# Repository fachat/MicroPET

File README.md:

# uPET R2

# NOTE: the newer version is in the [cbm_micropet](https://github.com/fachat/cbm_micropet) repository!

This is a re-incarnation of the Commodore PET computer(s) from the later 1970s.

It is build on a Eurocard board and has only parts that can still be obtained new in 2021.
The current version is 2.0B.

Here is the [Overview video](https://youtu.be/COlfqcaY7rI)

Some more videos on the build process can be found here [YT 8-bit times](https://youtube.com/playlist?list=PLi1dzy7kw1iybjcUccgjCV4fhNH4IPWSx)

## Features

The board is built with a number of features:

- Commodore 3032 / 4032 / 8032 / 8296 with options menu to select at boot
  - Boot-menu to select different PET versions to run (BASIC 1, 2, 4)
  - 40 col character display
  - 80 col character display
  - 8296 memory map emulation
  - IEEE488 interface (card edge and 24pin flat ribbon cable)
  - Tape connector (card edge)
  - PET graphics keyboard, or alternatively a C64 keyboard
- Improved system design:
  - 512k video RAM, plus 512k fast RAM, accessible using banks on the W65816 CPU
  - boot from an SPI Flash ROM
  - up to 12.5 MHz mode (via configuration register)
  - VGA b/w video output
  - Write protection for the PET ROMs once copied to RAM
  - lower 32k RAM mappable from all of the 512k fast RAM
- Improved Video output:
  - Hires graphics mode (using a configuration register)
  - modifyable character set
  - 40/80 column display switchable
  - 25/50 rows display switch
  - multiple video pages mappable to $8000 video mem address

## Overview

The system architecture is actually rather simple, as you can see in the following graphics.

The main functionality is "hidden" inside the CPLD. It does:

1. clock generation and management
2. memory mapping
3. video generation.
4. SPI interface and boot

On the CPU side of the CPLD it is actually a rather almost normal 65816 computer, 
with the exception that the bank register (that catches and stores the address lines 
A16-23 from the CPU's data bus) is in the CPLD, and that there is no ROM. The ROM has been
replaced with some code in the CPLD that copies the initial program to the CPU accessible
RAM, taking it from the Flash Boot ROM via SPI. This actually simplifies the design,
as 

1. parallel ROMs are getting harder to come by and
2. they are typically not as fast as is needed, and
3. with the SPI boot they don't occupy valuable CPU address space.

The video generation is done using time-sharing access to the video RAM.
The VGA output is 640x480 at 60Hz. So there is a 40ns slot per pixel on the screen, 
with a pixel clock of 25MHz.

The system runs at 12.5MHz, so a byte of pixel output (i.e. eight pixels) has four
memory accesses to VRAM. Two of them are reserved for video access, one for fetching the
character data (e.g. at $08xxx in the PET), and the second one to fetch the "character ROM"
data, i.e. the pixel data for a character. This is also stored in VRAM, and is being loaded
there from the Flash Boot ROM by the initial boot loader.

The CPLD reads the character data, stores it to fetch the character pixel data, and streams
that out using its internal video shift register.

For more detailled descriptions of the features and how to use them, pls see the subdirectory,
as described in the next section.

## Building

Here are four subdirectories:

- [Board](Board/) that contains the board schematics and layout
- [CPLD](CPLD/) contains the VHDL code to program the CPLD logic chip used, and describes the configuration options - including the [SPI](CPLD/SPI.md) usage
- [ROM](ROM/) ROM contents to boot
- [Case](Case/) 3-D printed supports and keyboards to mount board in a C64c case

### Board

To build the board, you have to find a provider that builds PCBs from Eagle .brd files.
Currently no gerbers are provided.

### CPLD

The CPLD is a Xilinx xc95288xl programmable logic chip. It runs on 3.3V, but is 5V tolerant,
so can be directly connected to 5V TTL chips. I programmed it in VHDL.

Unfortunately the W65xx parts are "only" CMOS, and not TTL input chips - but 3.3V is still above
the VCC/2 for the 5V chips. Only Phi2 needs improvements on the signal quality using a pull-up resistor
and specific VHDL programming.

### ROM

The ROM image can be built using gcc, xa65, and make. Use your favourite EPROM programmer to burn it into the SPI Flash chip.

The ROM contains images of all required ROM images for BASIC 1, 2, and 4, and corresponding editor ROMs, including
some that have been extended with wedges.

The updated editor ROMs are from [Steve's Editor ROM project](http://www.6502.org/users/sjgray/projects/editrom/index.html) and can handle C64 keyboards, has a DOS wedge included, and resets into the Micro-PET boot menu.
For more details see the [ROM description](ROM/README.md)

## Future Plans

These are future expansions I want to look into. Not all may be possible to implement.

- n/a

## Gallery

Note: the published schematics and board has the extra wires fixed/included.

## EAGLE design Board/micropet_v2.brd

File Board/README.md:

# Board V2.1A

The board is a two-layer Eurocard, i.e. 160mm x 100mm.

## Schematics & Layout

The schematics and layout have been created with Cadsoft Eagle.
So, here you can find the 

- [micropet_v2.sch](micropet_v2.sch) and
- [micropet_v2.brd](micropet_v2.brd) files

But, you can still have a look at the schematics and layout using the
PNG images created

- [micropet_v2-sch-1.png](micropet_v2-sch-1.png) Part 1 - PETIO
- [micropet_v2-sch-2.png](micropet_v2-sch-2.png) Part 2 - CPLD, CPU, RAM
- [micropet_v2-sch-3.png](micropet_v2-sch-3.png) Part 3 - Power
- [micropet_v2-sch-4.png](micropet_v2-sch-4.png) Part 4 - Video and Audio output
- [micropet_v2-sch-5.png](micropet_v2-sch-5.png) Part 5 - SPI devices (Eth, USB, RTCC, ...)

## Bill of Material

The main chips are:

- 1x W65816S CPU
- 2x W65C21N PIA
- 1x W65C22N VIA

- 1x xc95288xl CPLD
- 2x 8x512k parallel SRAM with 25ns access time
- 2x 74LS641-1
- 1x 74LS145 4-to-10 BCD O.C. driver (keyboard)
- 1x 74LS07
- 1x DS1813 RESET controller

- 50 MHZ crystal oscillator

- Voltage regulator

- x 0.1uF bypass caps

- 5.1kOhm / 2.4kOhm pairs of resistor arrays for IEEE488
- 10kOhm pullup
- 1x 1kOhm pullup
- 1x 8x10kOhm resistor array (keyboard pull up)

- div. resistors/caps to generate 3.3V output

More details can be found in the [Eagle parts list](micropet_v2.parts).

## Changelog

### V2.1A

In this version I incorporated the fixes I had to apply to the first prototype board. Also, I changed the IEEE488 circuit such that it can now really work as a disk drive for another PET. This brings it in line with the CSA PETIO 1.2A/1.3A boards that have this functionaly fixed.

## Erratum

This section describes fixes from my 2.0A prototype board, and these are the cuts/additional wires you see on the pictures, where I fixed my 2.0A boards.

### 2.0C

- I pulled up /IRQ to 5V, but that was potentially backfeeding to the 3.3V SPI devices. A pull-up to 3.3V still worked just fine without problems

### 2.0B

- In 2.0A I planned to use the 74245 to drive the system's Phi2 clocks (CPU & I/O), and to level-shift it. But it turned out that this was not stable, so I reverted to the pull-up resistor method again
- I was missing a cross-sheet connection for the I/O Phi2 clock
- Also I was missing the SPI select line for the RTCC

- 
-

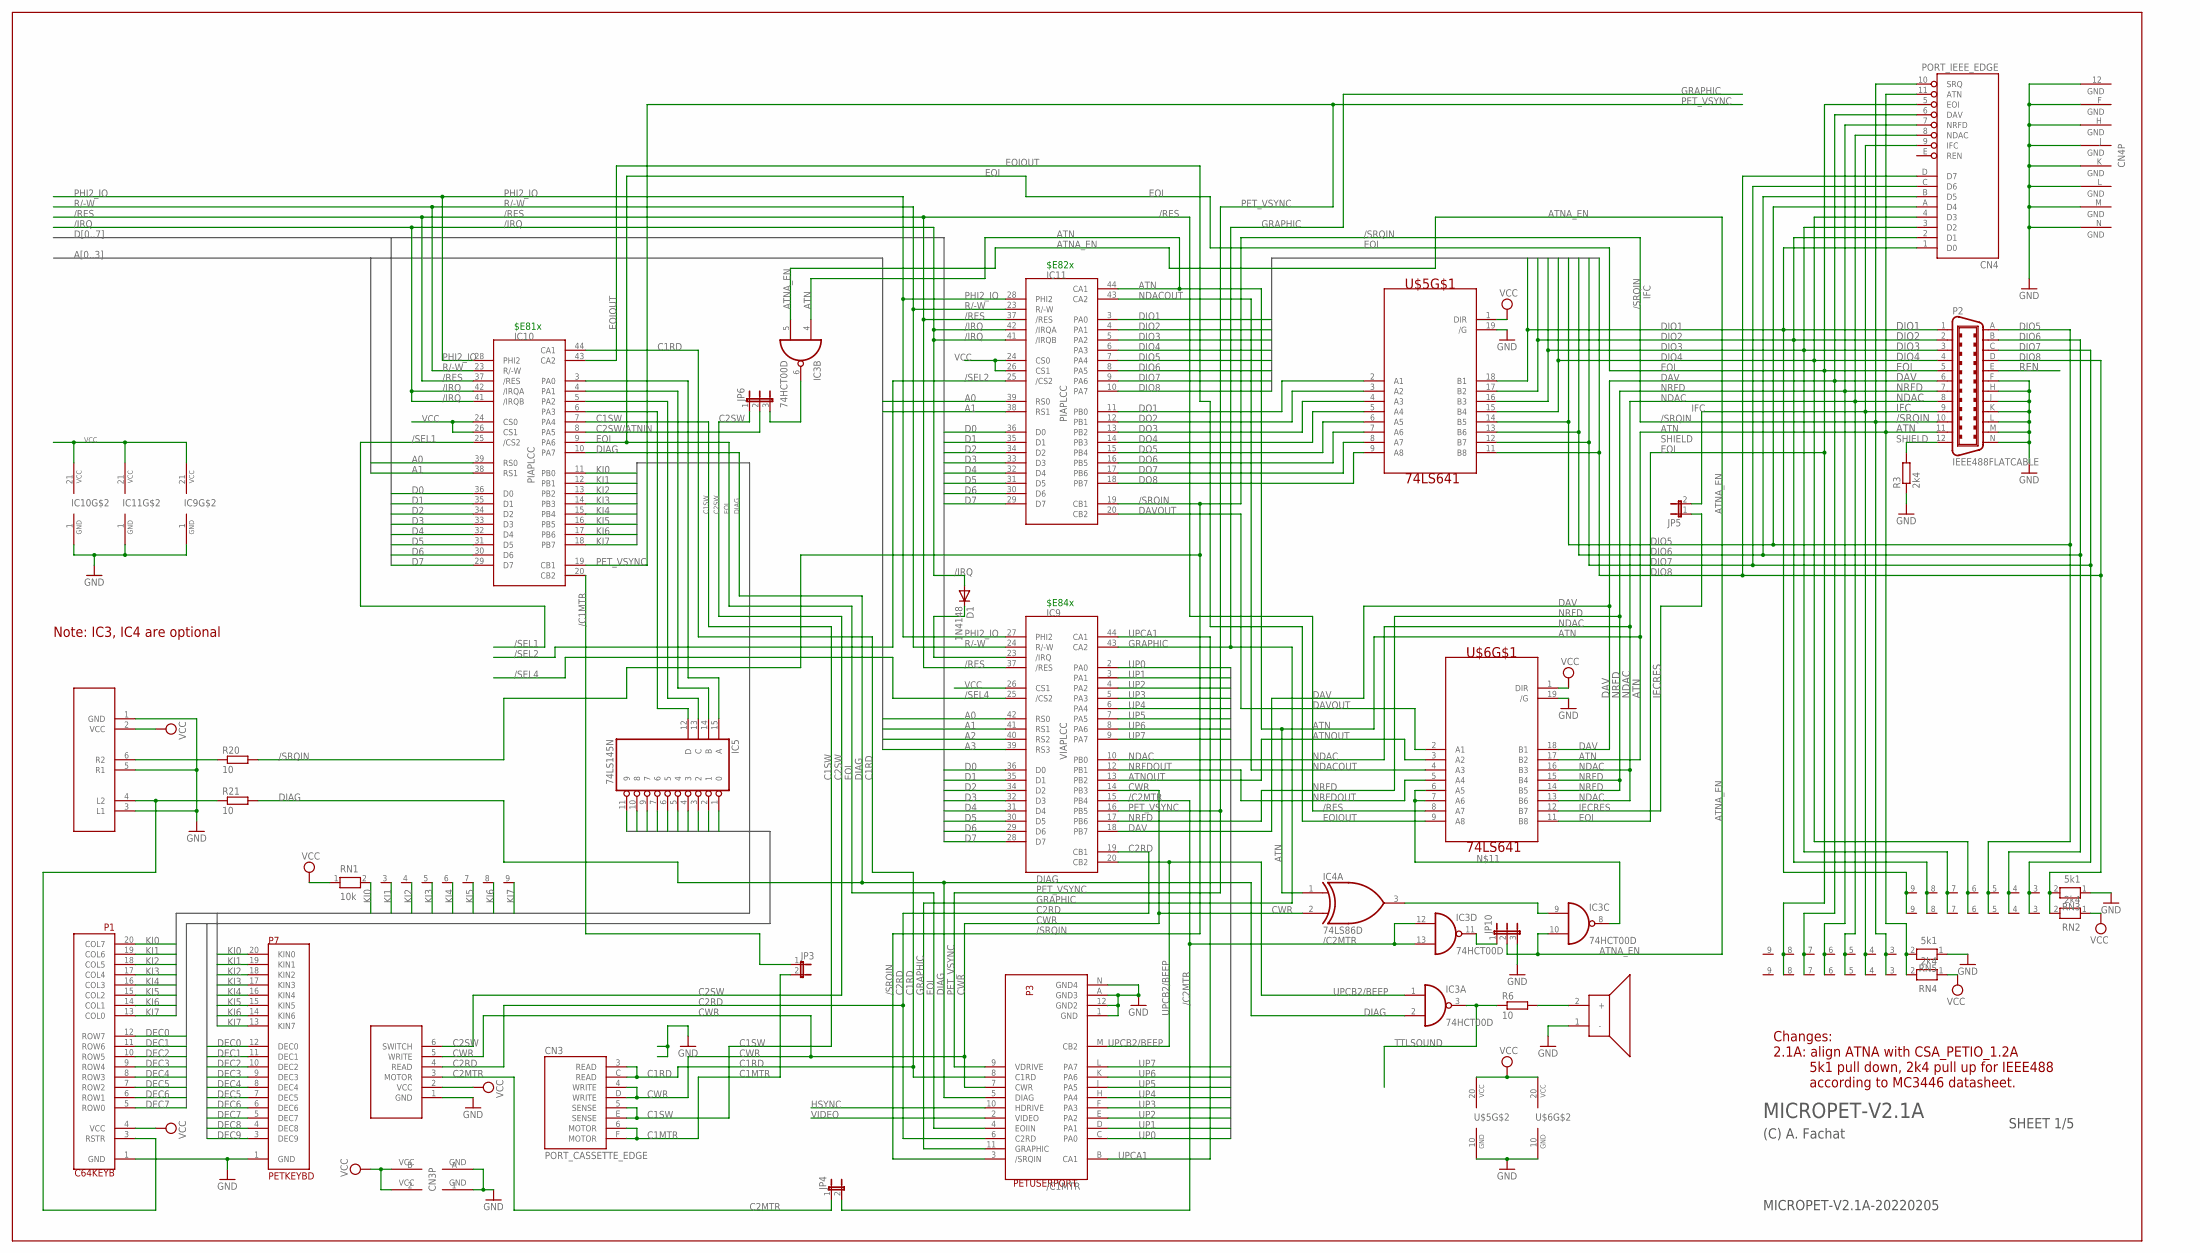
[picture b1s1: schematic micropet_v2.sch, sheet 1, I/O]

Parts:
BEEP1: PIEZOBEEPER; JP2
CN3: PORT_CASSETTE_EDGE; MA156_6-2_KEYED
CN4: PORT_IEEE_EDGE; MA156_12-2_IEEE
D1: 1N4148; D-5
IC3: 74HCT00D; SO14
IC4: 74LS86D; SO14
IC5: 74LS145N; DIL16
IC9: VIAPLCC; PLCC44
IC10, IC11: PIAPLCC; PLCC44
JP3, JP4, JP5: JP1E; JP1
JP6, JP10: JP2E; JP2
P1: C64KEYB
P2: IEEE488FLATCABLE; FLAT24
P3: PETUSERPORT; FLAT24
P6: CBMTAPE; JP6
P7: PETKEYBD; C64KEYB
R3: 2k4; 0207/2V
R6, R20, R21: 10; 0207/2V
RN1: 10k; RN-9
RN2, RN4: 2k4; RN-9
RN3, RN5: 5k1; RN-9
U$5, U$6: 74LS641; DIL20
U$11: PETSKEY_EXTRA; JP6

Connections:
/C1MTR: IC10.20 (CB2), JP3.1
/C2MTR: IC3.12 (I0), IC3.13 (I1), IC9.15 (PB4), JP4.2
/IRQ: D1.A, IC10.41 (/IRQB), IC10.42 (/IRQA), IC11.41 (/IRQB), IC11.42 (/IRQA); also elsewhere on the board
/RES: IC9.37 (/RES), IC10.37 (/RES), IC11.37 (/RES), U$6.8 (A7); also elsewhere on the board
/SEL1: IC10.25 (/CS2); also elsewhere on the board
/SEL2: IC11.25 (/CS2); also elsewhere on the board
/SEL4: IC9.25 (/CS2); also elsewhere on the board
/SRQIN: CN4.10 (SRQ), IC11.19 (CB1), P2.10, P3.3 (/SRQIN), R20.2, RN4.3, RN5.3
A0: IC9.42 (RS0), IC10.39 (RS0), IC11.39 (RS0); also elsewhere on the board
A1: IC9.41 (RS1), IC10.38 (RS1), IC11.38 (RS1); also elsewhere on the board
A2: IC9.40 (RS2); also elsewhere on the board
A3: IC9.39 (RS3); also elsewhere on the board
ATN: CN4.11 (ATN), IC3.4 (I0), IC4.1 (I0), IC11.44 (CA1), P2.11, RN4.2, RN5.2, U$6.17 (B2)
ATNA_EN: IC3.5 (I1), IC3.10 (I1), JP10.2
ATNOUT: IC9.13 (PB2), U$6.3 (A2)
C1MTR: CN3.6 (MOTOR), CN3.F (MOTOR), JP3.2
C1RD: CN3.3 (READ), CN3.C (READ), IC10.44 (CA1), P3.8 (C1RD)
C1SW: CN3.5 (SENSE), CN3.E (SENSE), IC10.7 (PA4)
C2MTR: JP4.1, P6.3 (MOTOR)
C2RD: IC9.19 (CB1), P3.6 (C2RD), P6.4 (READ)
C2SW: JP6.1, P6.6 (SWITCH)
C2SW/ATNIN: IC10.8 (PA5), JP6.2
CWR: CN3.4 (WRITE), CN3.D (WRITE), IC4.2 (I1), IC9.14 (PB3), P3.7 (CWR), P6.5 (WRITE)
D0: IC9.36 (D0), IC10.36 (D0), IC11.36 (D0); also elsewhere on the board
D1: IC9.35 (D1), IC10.35 (D1), IC11.35 (D1); also elsewhere on the board
D2: IC9.34 (D2), IC10.34 (D2), IC11.34 (D2); also elsewhere on the board
D3: IC9.32 (D3), IC10.33 (D3), IC11.33 (D3); also elsewhere on the board
D4: IC9.31 (D4), IC10.32 (D4), IC11.32 (D4); also elsewhere on the board
D5: IC9.30 (D5), IC10.31 (D5), IC11.31 (D5); also elsewhere on the board
D6: IC9.29 (D6), IC10.30 (D6), IC11.30 (D6); also elsewhere on the board
D7: IC9.28 (D7), IC10.29 (D7), IC11.29 (D7); also elsewhere on the board
DAV: CN4.6 (DAV), IC9.18 (PB7), P2.6, RN4.7, RN5.7, U$6.18 (B1)
DAVOUT: IC11.20 (CB2), U$6.2 (A1)
DEC0: IC5.1 (0), P1.12 (ROW7), P7.12 (DEC0)
DEC1: IC5.2 (1), P1.11 (ROW6), P7.11 (DEC1)
DEC2: IC5.3 (2), P1.10 (ROW5), P7.10 (DEC2)
DEC3: IC5.4 (3), P1.9 (ROW4), P7.9 (DEC3)
DEC4: IC5.5 (4), P1.8 (ROW3), P7.8 (DEC4)
DEC5: IC5.6 (5), P1.7 (ROW2), P7.7 (DEC5)
DEC6: IC5.7 (6), P1.6 (ROW1), P7.6 (DEC6)
DEC7: IC5.9 (7), P1.5 (ROW0), P7.5 (DEC7)
DEC8: IC5.10 (8), P7.4 (DEC8)
DEC9: IC5.11 (9), P7.3 (DEC9)
DIAG: IC3.2 (I1), IC10.10 (PA7), P3.5 (DIAG), R21.2
DIO1: CN4.1 (D0), IC11.3 (PA0), P2.1, RN2.9, RN3.9, U$5.18 (B1)
DIO2: CN4.2 (D1), IC11.4 (PA1), P2.2, RN2.8, RN3.8, U$5.17 (B2)
DIO3: CN4.3 (D2), IC11.5 (PA2), P2.3, RN2.7, RN3.7, U$5.16 (B3)
DIO4: CN4.4 (D3), IC11.6 (PA3), P2.4, RN2.6, RN3.6, U$5.15 (B4)
DIO5: CN4.A (D4), IC11.7 (PA4), P2.A (13), RN2.5, RN3.5, U$5.14 (B5)
DIO6: CN4.B (D5), IC11.8 (PA5), P2.B (14), RN2.4, RN3.4, U$5.13 (B6)
DIO7: CN4.C (D6), IC11.9 (PA6), P2.C (15), RN2.3, RN3.3, U$5.12 (B7)
DIO8: CN4.D (D7), IC11.10 (PA7), P2.D (16), RN2.2, RN3.2, U$5.11 (B8)
DO1: IC11.11 (PB0), U$5.2 (A1)
DO2: IC11.12 (PB1), U$5.3 (A2)
DO3: IC11.13 (PB2), U$5.4 (A3)
DO4: IC11.14 (PB3), U$5.5 (A4)
DO5: IC11.15 (PB4), U$5.6 (A5)
DO6: IC11.16 (PB5), U$5.7 (A6)
DO7: IC11.17 (PB6), U$5.8 (A7)
DO8: IC11.18 (PB7), U$5.9 (A8)
EOI: CN4.5 (EOI), IC10.9 (PA6), P2.5, P3.4 (EOIIN), RN4.8, RN5.8, U$6.11 (B8)
EOIOUT: IC10.43 (CA2), U$6.9 (A8)
GND: BEEP1.1 (-), CN3.1 (GND), CN3.A (GND), CN4.12 (GND), CN4.F (GND), CN4.H (GND), CN4.J (GND), CN4.K (GND), CN4.L (GND), CN4.M (GND), CN4.N (GND), IC3.7 (GND), IC4.7 (GND), IC5.8 (GND), IC9.1 (GND), IC10.1 (GND), IC11.1 (GND), JP10.3, P1.1 (GND), P2.F (18), P2.H (19), P2.J (20), P2.K (21), P2.L (22), P2.M (23), P2.N (24), P3.1 (GND), P3.12 (GND2), P3.A (GND3), P3.N (GND4), P6.1 (GND), P7.1 (GND), R3.1, RN3.1, RN5.1, U$5.10 (GND), U$5.19 (/G), U$6.10 (GND), U$6.19 (/G), U$11.1 (GND), U$11.3 (L1), U$11.5 (R1); also elsewhere on the board
GRAPHIC: IC9.43 (CA2), P3.11 (GRAPHIC); also elsewhere on the board
HSYNC: P3.10 (HDRIVE); also elsewhere on the board
IECRES: JP5.1, U$6.12 (B7)
IFC: CN4.9 (IFC), JP5.2, P2.9, RN4.4, RN5.4
KI0: IC10.11 (PB0), P1.20 (COL7), P7.20 (KIN0), RN1.2
KI1: IC10.12 (PB1), P1.19 (COL6), P7.19 (KIN1), RN1.3
KI2: IC10.13 (PB2), P1.18 (COL5), P7.18 (KIN2), RN1.4
KI3: IC10.14 (PB3), P1.17 (COL4), P7.17 (KIN3), RN1.5
KI4: IC10.15 (PB4), P1.16 (COL3), P7.16 (KIN4), RN1.6
KI5: IC10.16 (PB5), P1.15 (COL2), P7.15 (KIN5), RN1.7
KI6: IC10.17 (PB6), P1.14 (COL1), P7.14 (KIN6), RN1.8
KI7: IC10.18 (PB7), P1.13 (COL0), P7.13 (KIN7), RN1.9
unnamed: IC3.9 (I0), IC4.3 (O)
unnamed: IC3.11 (O), JP10.1
unnamed: BEEP1.2 (+), R6.2
unnamed: D1.C, IC9.23 (/IRQ)
unnamed: IC3.8 (O), U$6.6 (A5), U$6.7 (A6)
unnamed: IC3.6 (O), JP6.3
unnamed: IC5.15 (A), IC10.3 (PA0)
unnamed: IC5.14 (B), IC10.4 (PA1)
unnamed: IC5.13 (C), IC10.5 (PA2)
unnamed: IC5.12 (D), IC10.6 (PA3)
unnamed: P1.3 (RSTR), R21.1, U$11.4 (L2)
unnamed: R20.1, U$11.6 (R2)
NDAC: CN4.8 (NDAC), IC9.10 (PB0), P2.8, RN4.5, RN5.5, U$6.13 (B6), U$6.16 (B3)
NDACOUT: IC11.43 (CA2), U$6.4 (A3)
NRFD: CN4.7 (NRFD), IC9.17 (PB6), P2.7, RN4.6, RN5.6, U$6.14 (B5), U$6.15 (B4)
NRFDOUT: IC9.12 (PB1), U$6.5 (A4)
PET_VSYNC: IC9.16 (PB5), IC10.19 (CB1), P3.9 (VDRIVE); also elsewhere on the board
PHI2_IO: IC9.27 (PHI2), IC10.28 (PHI2), IC11.28 (PHI2); also elsewhere on the board
R/-W: IC9.24 (R/-W), IC10.23 (R/-W), IC11.23 (R/-W); also elsewhere on the board
REN: P2.E (17)
SHIELD: P2.12, R3.2
TTLSOUND: IC3.3 (O), R6.1; also elsewhere on the board
UP0: IC9.2 (PA0), P3.C (PA0)
UP1: IC9.3 (PA1), P3.D (PA1)
UP2: IC9.4 (PA2), P3.E (PA2)
UP3: IC9.5 (PA3), P3.F (PA3)
UP4: IC9.6 (PA4), P3.H (PA4)
UP5: IC9.7 (PA5), P3.J (PA5)
UP6: IC9.8 (PA6), P3.K (PA6)
UP7: IC9.9 (PA7), P3.L (PA7)
UPCA1: IC9.44 (CA1), P3.B (CA1)
UPCB2/BEEP: IC3.1 (I0), IC9.20 (CB2), P3.M (CB2)
VCC: CN3.2 (VCC), CN3.B (VCC), IC3.14 (VCC), IC4.14 (VCC), IC5.16 (VCC), IC9.21 (VCC), IC9.26 (CS1), IC10.21 (VCC), IC10.24 (CS0), IC10.26 (CS1), IC11.21 (VCC), IC11.24 (CS0), IC11.26 (CS1), P1.4 (VCC), P6.2 (VCC), RN1.1, RN2.1, RN4.1, U$5.1 (DIR), U$5.20 (VCC), U$6.1 (DIR), U$6.20 (VCC), U$11.2 (VCC); also elsewhere on the board
VIDEO: P3.2 (VIDEO); also elsewhere on the board

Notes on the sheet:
MICROPET-V2.1A-20220205
MICROPET-V2.1A
(C) A. Fachat
$E82x
$E84x
$E81x
SHEET 1/5
Note: IC3, IC4 are optional
Changes: 2.1A: align ATNA with CSA_PETIO_1.2A 5k1 pull down, 2k4 pull up for IEEE488 according to MC3446 datasheet.

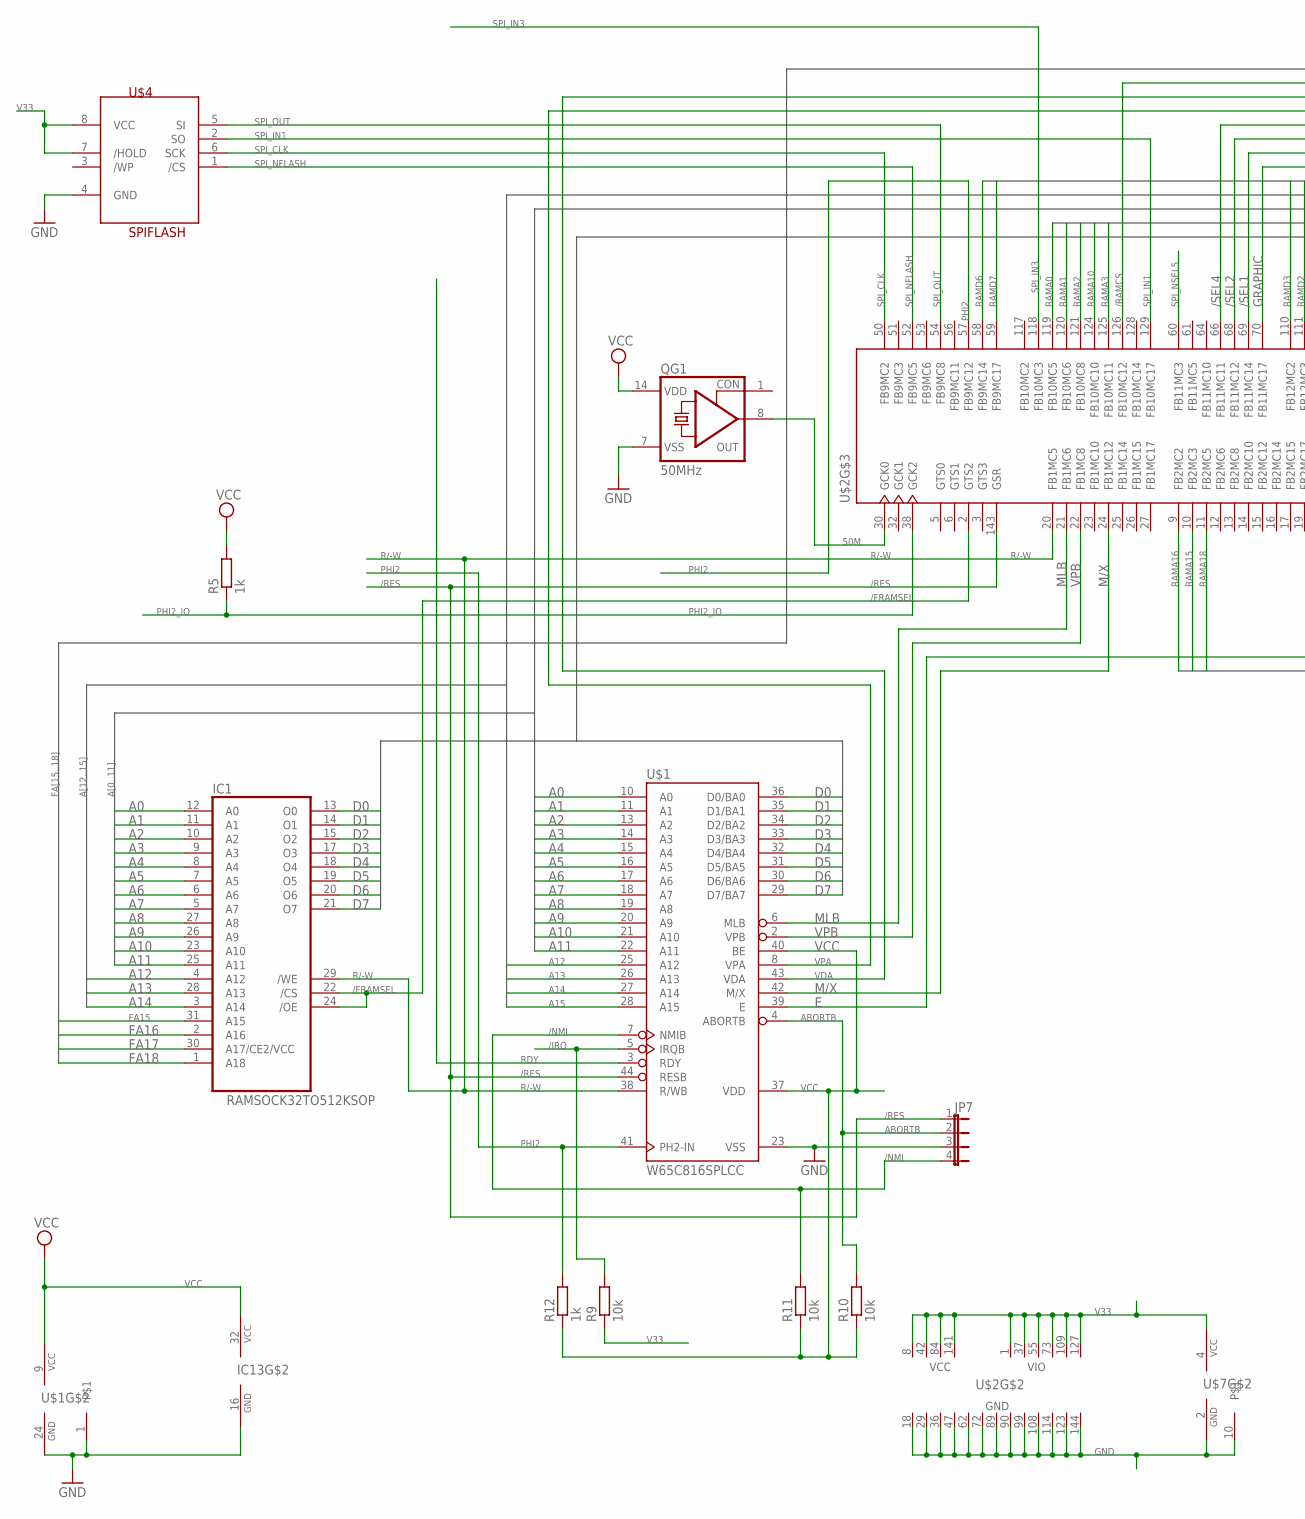
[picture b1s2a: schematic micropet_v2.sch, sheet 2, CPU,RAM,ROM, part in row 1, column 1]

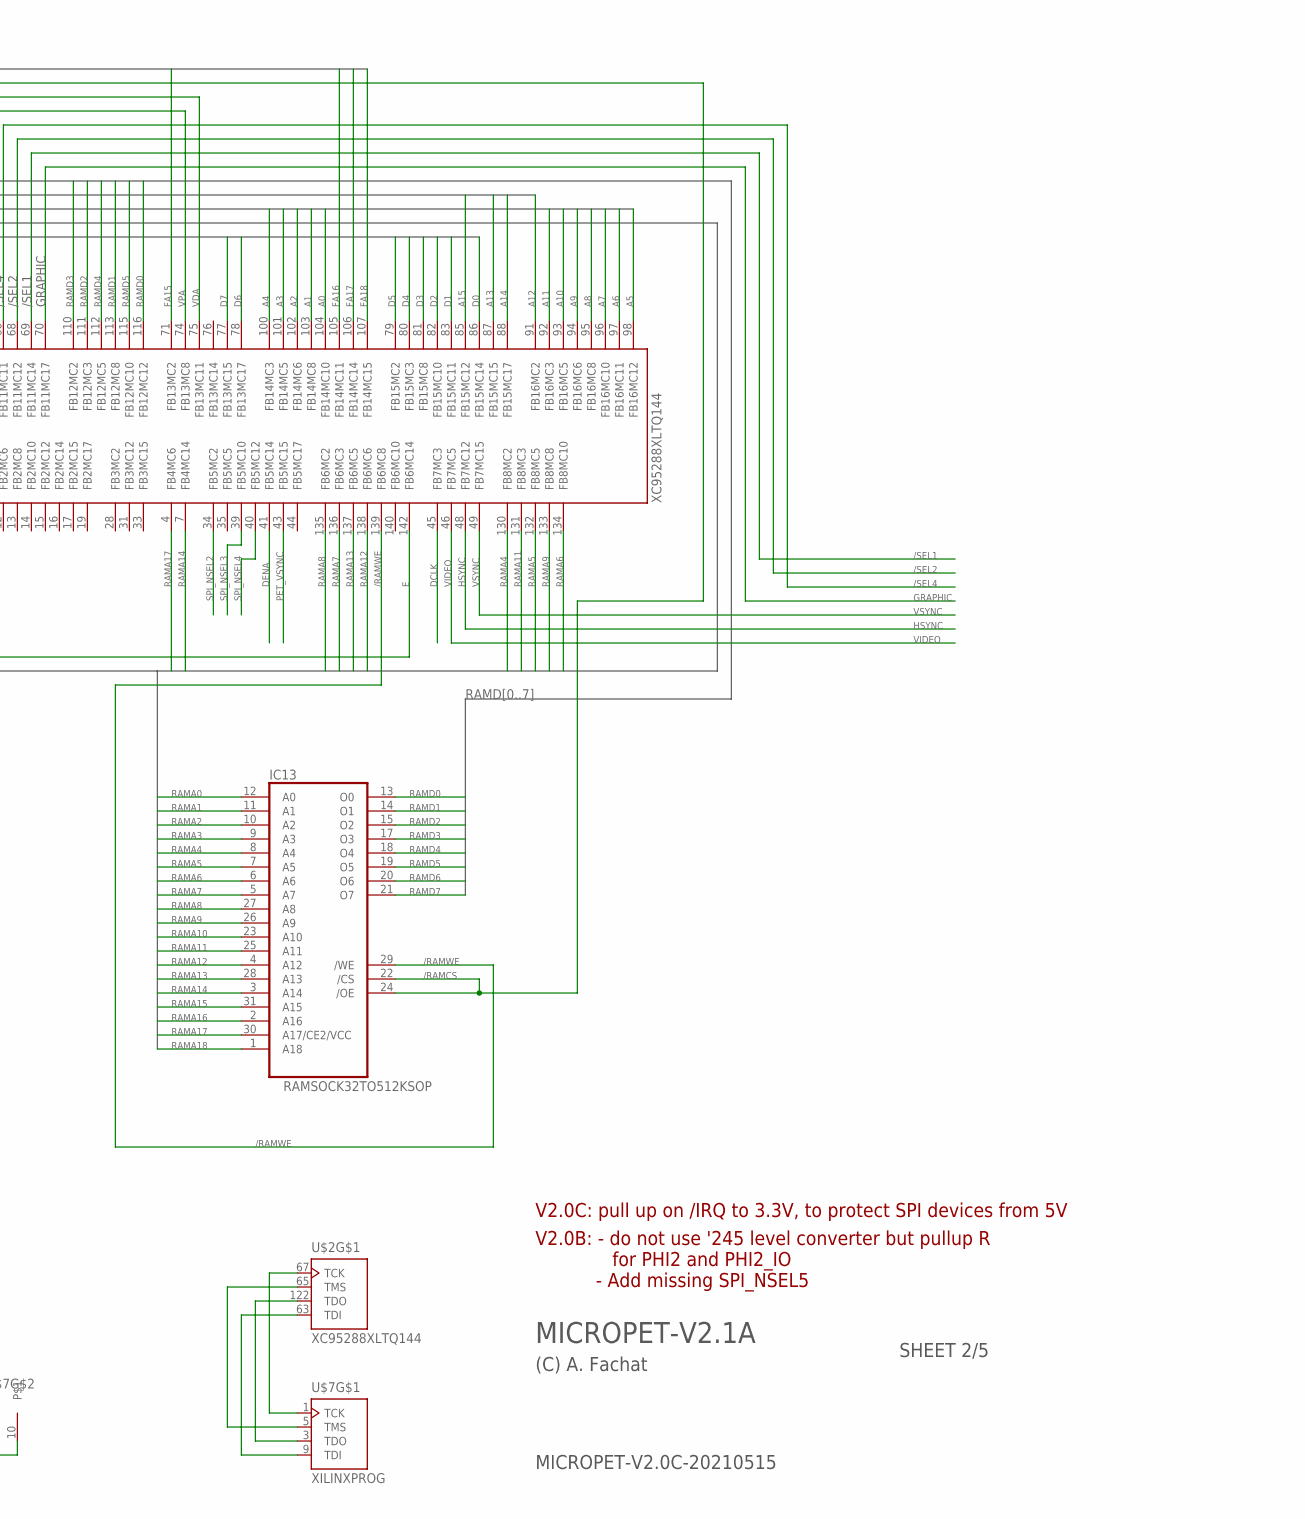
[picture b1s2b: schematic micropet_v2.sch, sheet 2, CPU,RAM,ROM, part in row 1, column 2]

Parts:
IC1, IC13: RAMSOCK32TO512KSOP; SOP32
JP7: JP4E; JP4
QG1: 50MHz; SG51
R5, R12: 1k; 0207/2V
R9, R10, R11: 10k; 0207/2V
U$1: W65C816SPLCC; PLCC44
U$2: XC95288XLTQ144; TQFP144
U$4: SPIFLASH; DIL08
U$7: XILINXPROG; FLAT10BOX

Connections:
50M: QG1.8 (OUT), U$2.30 (GCK0)
/FRAMSEL: IC1.22 (/CS), IC1.24 (/OE), U$2.2 (GTS2)
/IRQ: R9.2, U$1.5 (IRQB); also elsewhere on the board
/NMI: JP7.4, R11.2, U$1.7 (NMIB)
/RAMCS: IC13.22 (/CS), IC13.24 (/OE), U$2.126 (FB10MC12)
/RAMWE: IC13.29 (/WE), U$2.139 (FB6MC8)
/RES: JP7.1, U$1.44 (RESB), U$2.143 (GSR); also elsewhere on the board
/SEL1: U$2.69 (FB11MC14); also elsewhere on the board
/SEL2: U$2.68 (FB11MC12); also elsewhere on the board
/SEL4: U$2.66 (FB11MC11); also elsewhere on the board
A0: IC1.12 (A0), U$1.10 (A0), U$2.104 (FB14MC10); also elsewhere on the board
A1: IC1.11 (A1), U$1.11 (A1), U$2.103 (FB14MC8); also elsewhere on the board
A2: IC1.10 (A2), U$1.13 (A2), U$2.102 (FB14MC6); also elsewhere on the board
A3: IC1.9 (A3), U$1.14 (A3), U$2.101 (FB14MC5); also elsewhere on the board
A4: IC1.8 (A4), U$1.15 (A4), U$2.100 (FB14MC3)
A5: IC1.7 (A5), U$1.16 (A5), U$2.98 (FB16MC12)
A6: IC1.6 (A6), U$1.17 (A6), U$2.97 (FB16MC11)
A7: IC1.5 (A7), U$1.18 (A7), U$2.96 (FB16MC10)
A8: IC1.27 (A8), U$1.19 (A8), U$2.95 (FB16MC8)
A9: IC1.26 (A9), U$1.20 (A9), U$2.94 (FB16MC6)
A10: IC1.23 (A10), U$1.21 (A10), U$2.93 (FB16MC5)
A11: IC1.25 (A11), U$1.22 (A11), U$2.92 (FB16MC3)
A12: IC1.4 (A12), U$1.25 (A12), U$2.91 (FB16MC2)
A13: IC1.28 (A13), U$1.26 (A13), U$2.87 (FB15MC15)
A14: IC1.3 (A14), U$1.27 (A14), U$2.88 (FB15MC17)
A15: U$1.28 (A15), U$2.85 (FB15MC12)
ABORTB: JP7.2, R10.2, U$1.4 (ABORTB)
D0: IC1.13 (O0), U$1.36 (D0/BA0), U$2.86 (FB15MC14); also elsewhere on the board
D1: IC1.14 (O1), U$1.35 (D1/BA1), U$2.83 (FB15MC11); also elsewhere on the board
D2: IC1.15 (O2), U$1.34 (D2/BA2), U$2.82 (FB15MC10); also elsewhere on the board
D3: IC1.17 (O3), U$1.33 (D3/BA3), U$2.81 (FB15MC8); also elsewhere on the board
D4: IC1.18 (O4), U$1.32 (D4/BA4), U$2.80 (FB15MC3); also elsewhere on the board
D5: IC1.19 (O5), U$1.31 (D5/BA5), U$2.79 (FB15MC2); also elsewhere on the board
D6: IC1.20 (O6), U$1.30 (D6/BA6), U$2.78 (FB13MC17); also elsewhere on the board
D7: IC1.21 (O7), U$1.29 (D7/BA7), U$2.77 (FB13MC15); also elsewhere on the board
DCLK: U$2.45 (FB7MC3); also elsewhere on the board
DENA: U$2.41 (FB5MC14); also elsewhere on the board
E: U$1.39 (E), U$2.142 (FB6MC14)
FA15: IC1.31 (A15), U$2.71 (FB13MC2)
FA16: IC1.2 (A16), U$2.105 (FB14MC11)
FA17: IC1.30 (A17/CE2/VCC), U$2.106 (FB14MC14)
FA18: IC1.1 (A18), U$2.107 (FB14MC15)
GND: IC1.16 (GND), IC13.16 (GND), JP7.3, QG1.7 (VSS), U$1.1, U$1.23 (VSS), U$1.24 (GND), U$2.18 (GND), U$2.29 (GND), U$2.36 (GND), U$2.47 (GND), U$2.62 (GND), U$2.72 (GND), U$2.89 (GND), U$2.90 (GND), U$2.99 (GND), U$2.108 (GND), U$2.114 (GND), U$2.123 (GND), U$2.144 (GND), U$4.4 (GND), U$7.2 (GND), U$7.10; also elsewhere on the board
GRAPHIC: U$2.70 (FB11MC17); also elsewhere on the board
HSYNC: U$2.48 (FB7MC12); also elsewhere on the board
M/X: U$1.42 (M/X), U$2.24 (FB1MC12)
MLB: U$1.6 (MLB), U$2.21 (FB1MC6)
PET_VSYNC: U$2.43 (FB5MC15); also elsewhere on the board
PHI2: R12.2, U$1.41 (PH2-IN), U$2.57 (FB9MC12)
PHI2_IO: R5.1, U$2.38 (GCK2); also elsewhere on the board
R/-W: IC1.29 (/WE), U$1.38 (R/WB), U$2.20 (FB1MC5); also elsewhere on the board
RAMA0: IC13.12 (A0), U$2.119 (FB10MC5)
RAMA1: IC13.11 (A1), U$2.120 (FB10MC6)
RAMA2: IC13.10 (A2), U$2.121 (FB10MC8)
RAMA3: IC13.9 (A3), U$2.125 (FB10MC11)
RAMA4: IC13.8 (A4), U$2.130 (FB8MC2)
RAMA5: IC13.7 (A5), U$2.132 (FB8MC5)
RAMA6: IC13.6 (A6), U$2.134 (FB8MC10)
RAMA7: IC13.5 (A7), U$2.136 (FB6MC3)
RAMA8: IC13.27 (A8), U$2.135 (FB6MC2)
RAMA9: IC13.26 (A9), U$2.133 (FB8MC8)
RAMA10: IC13.23 (A10), U$2.124 (FB10MC10)
RAMA11: IC13.25 (A11), U$2.131 (FB8MC3)
RAMA12: IC13.4 (A12), U$2.138 (FB6MC6)
RAMA13: IC13.28 (A13), U$2.137 (FB6MC5)
RAMA14: IC13.3 (A14), U$2.7 (FB4MC14)
RAMA15: IC13.31 (A15), U$2.10 (FB2MC3)
RAMA16: IC13.2 (A16), U$2.9 (FB2MC2)
RAMA17: IC13.30 (A17/CE2/VCC), U$2.4 (FB4MC6)
RAMA18: IC13.1 (A18), U$2.11 (FB2MC5)
RAMD0: IC13.13 (O0), U$2.116 (FB12MC12)
RAMD1: IC13.14 (O1), U$2.113 (FB12MC8)
RAMD2: IC13.15 (O2), U$2.111 (FB12MC3)
RAMD3: IC13.17 (O3), U$2.110 (FB12MC2)
RAMD4: IC13.18 (O4), U$2.112 (FB12MC5)
RAMD5: IC13.19 (O5), U$2.115 (FB12MC10)
RAMD6: IC13.20 (O6), U$2.58 (FB9MC14)
RAMD7: IC13.21 (O7), U$2.59 (FB9MC17)
RDY: U$1.3 (RDY)
SPI_CLK: U$2.50 (FB9MC2), U$4.6 (SCK); also elsewhere on the board
SPI_IN1: U$2.129 (FB10MC17), U$4.2 (SO); also elsewhere on the board
SPI_IN3: U$2.118 (FB10MC3); also elsewhere on the board
SPI_NFLASH: U$2.52 (FB9MC5), U$4.1 (/CS)
SPI_NSEL2: U$2.34 (FB5MC2); also elsewhere on the board
SPI_NSEL3: U$2.39 (FB5MC10); also elsewhere on the board
SPI_NSEL4: U$2.40 (FB5MC12); also elsewhere on the board
SPI_NSEL5: U$2.60 (FB11MC3); also elsewhere on the board
SPI_OUT: U$2.54 (FB9MC8), U$4.5 (SI); also elsewhere on the board
TCK: U$2.67 (TCK), U$7.1 (TCK)
TDI: U$2.63 (TDI), U$7.9 (TDI)
TDO: U$2.122 (TDO), U$7.3 (TDO)
TMS: U$2.65 (TMS), U$7.5 (TMS)
V33: R9.1, U$2.1 (VIO), U$2.8 (VCC), U$2.37 (VIO), U$2.42 (VCC), U$2.55 (VIO), U$2.73 (VIO), U$2.84 (VCC), U$2.109 (VIO), U$2.127 (VIO), U$2.141 (VCC), U$4.7 (/HOLD), U$4.8 (VCC), U$7.4 (VCC); also elsewhere on the board
VCC: IC1.32 (VCC), IC13.32 (VCC), QG1.14 (VDD), R5.2, R10.1, R11.1, R12.1, U$1.9 (VCC), U$1.37 (VDD), U$1.40 (BE); also elsewhere on the board
VDA: U$1.43 (VDA), U$2.75 (FB13MC11)
VIDEO: U$2.46 (FB7MC5); also elsewhere on the board
VPA: U$1.8 (VPA), U$2.74 (FB13MC8)
VPB: U$1.2 (VPB), U$2.22 (FB1MC8)
VSYNC: U$2.49 (FB7MC15); also elsewhere on the board

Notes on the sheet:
MICROPET-V2.0C-20210515
MICROPET-V2.1A
(C) A. Fachat
SHEET 2/5
V2.0C: pull up on /IRQ to 3.3V, to protect SPI devices from 5V
V2.0B: - do not use '245 level converter but pullup R for PHI2 and PHI2_IO - Add missing SPI_NSEL5

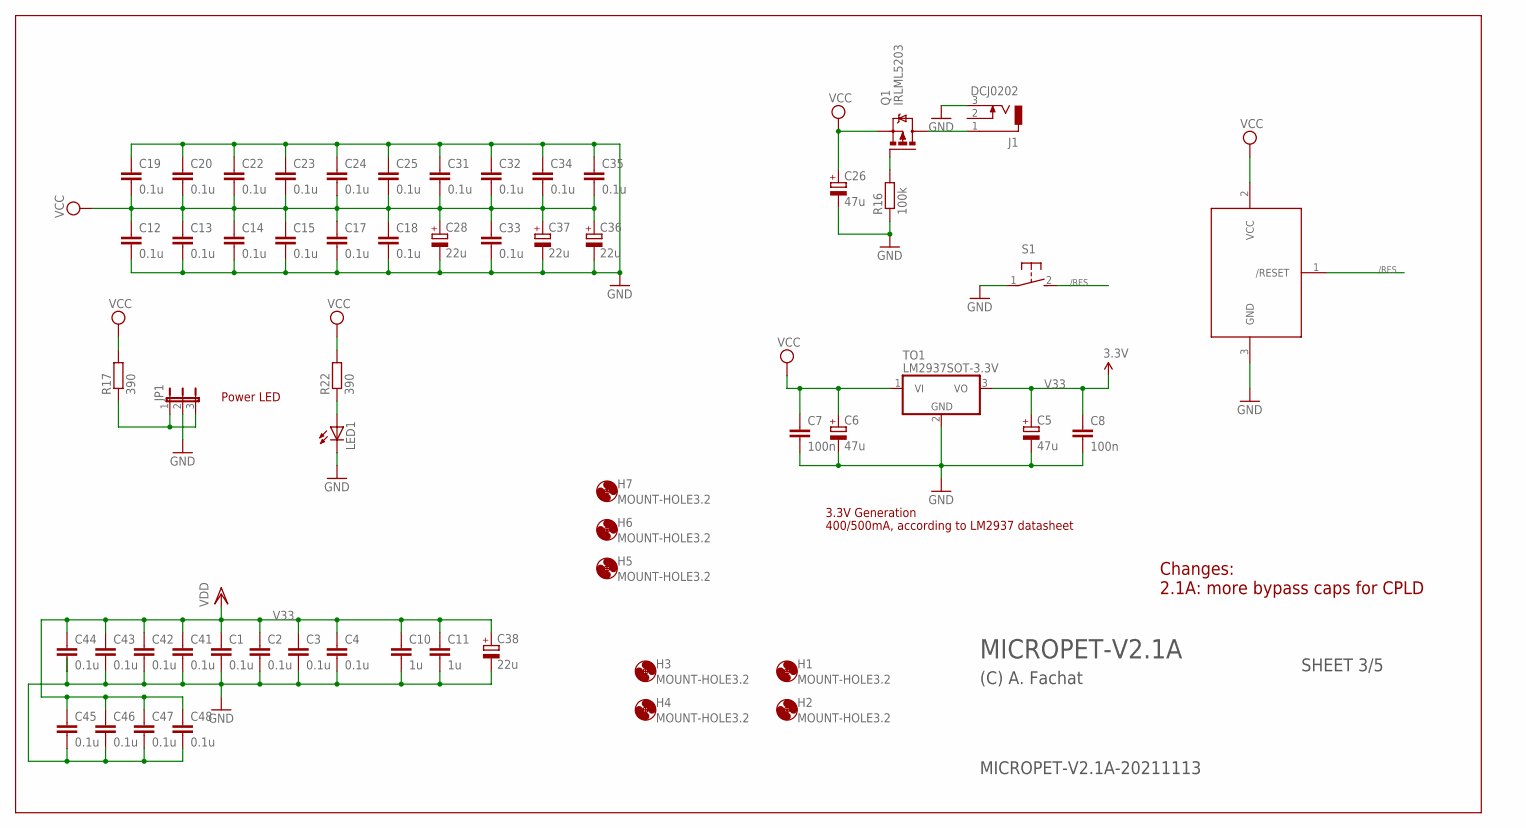
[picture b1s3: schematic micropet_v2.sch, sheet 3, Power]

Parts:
C1, C2, C3, C4, C12, C13, C14, C15, C17, C18, C19, C20, C22, C23, C24, C25, C31, C32, C33, C34, C35, C41, C42, C43, C44, C45, C46, C47, C48: 0.1u; C0603
C5: 47u; E5-8,5
C6: 47u; E5-6
C7, C8: 100n; C0603
C10, C11: 1u; C0603
C26: 47u; E2,5-6
C28, C36, C37, C38: 22u; E2,5-6
H1, H2, H3, H4, H5, H6, H7: MOUNT-HOLE3.2; 3,2
J1: DCJ0202
JP1: JP2E; JP2
LED1: LED3MM
Q1: IRLML5203; MICRO3
R16: 100k; 0207/2V
R17, R22: 390; 0207/2V
S1: 31-XX; B3F-31XX
TO1: LM2937SOT-3.3V; SOT223
U$3: DS1813; TO92

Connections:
/RES: S1.2 (S), U$3.1 (/RESET); also elsewhere on the board
GND: C1.2, C2.2, C3.2, C4.2, C5.-, C6.-, C7.2, C8.2, C10.2, C11.2, C12.2, C13.2, C14.2, C15.2, C17.2, C18.2, C19.1, C20.1, C22.1, C23.1, C24.1, C25.1, C26.-, C28.-, C31.1, C32.1, C33.2, C34.1, C35.1, C36.-, C37.-, C38.-, C41.2, C42.2, C43.2, C44.2, C45.2, C46.2, C47.2, C48.2, J1.3, JP1.2, LED1.K (C), R16.1, S1.1, TO1.2 (GND), U$3.3 (GND); also elsewhere on the board
unnamed: J1.1, Q1.3 (D)
unnamed: Q1.1 (G), R16.2
unnamed: JP1.1, JP1.3, R17.1
unnamed: LED1.A, R22.1
V33: C1.1, C2.1, C3.1, C4.1, C5.+, C8.1, C10.1, C11.1, C38.+, C41.1, C42.1, C43.1, C44.1, C45.1, C46.1, C47.1, C48.1, TO1.3 (VO); also elsewhere on the board
VCC: C6.+, C7.1, C12.1, C13.1, C14.1, C15.1, C17.1, C18.1, C19.2, C20.2, C22.2, C23.2, C24.2, C25.2, C26.+, C28.+, C31.2, C32.2, C33.1, C34.2, C35.2, C36.+, C37.+, Q1.2 (S), R17.2, R22.2, TO1.1 (VI), U$3.2 (VCC); also elsewhere on the board

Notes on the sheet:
MICROPET-V2.1A-20211113
MICROPET-V2.1A
(C) A. Fachat
SHEET 3/5
3.3V Generation
400/500mA, according to LM2937 datasheet
Power LED
Changes: 2.1A: more bypass caps for CPLD

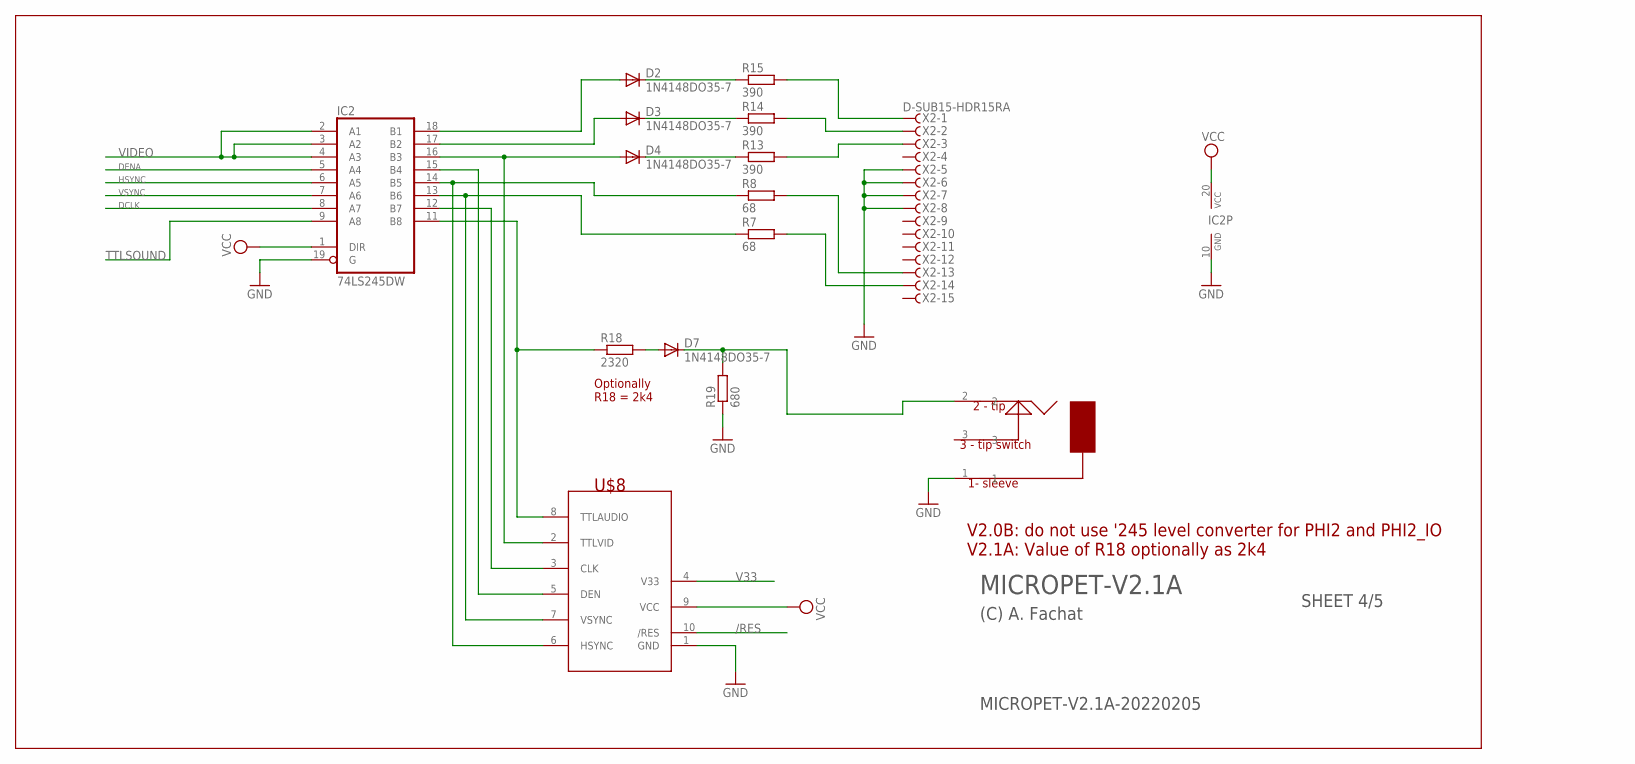
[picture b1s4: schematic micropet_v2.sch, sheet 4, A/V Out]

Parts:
D2, D3, D4, D7: 1N4148DO35-7; DO35-7
IC2: 74LS245DW; SO20W
R7, R8: 68; 0204V
R13, R14, R15: 390; 0204V
R18: 2320; 0204V
R19: 680; 0204V
U$8: MONOVIDAUDIO; FLAT10RIB
U$10: MONOAUDIOB; CUI_MJ-3502-B
X2: D-SUB15-HDR15RA; HDR15RA

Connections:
/RES: U$8.10 (/RES); also elsewhere on the board
DCLK: IC2.8 (A7); also elsewhere on the board
DENA: IC2.5 (A4); also elsewhere on the board
GND: IC2.10 (GND), IC2.19 (G), R19.1, U$8.1 (GND), U$10.1, X2.5, X2.6, X2.7, X2.8; also elsewhere on the board
HSYNC: IC2.6 (A5); also elsewhere on the board
unnamed: IC2.11 (B8), R18.1, U$8.8 (TTLAUDIO)
unnamed: D2.A, IC2.18 (B1)
unnamed: IC2.13 (B6), R7.1, U$8.7 (VSYNC)
unnamed: IC2.12 (B7), U$8.3 (CLK)
unnamed: R15.2, X2.1
unnamed: R14.2, X2.2
unnamed: R13.2, X2.3
unnamed: R8.2, X2.13
unnamed: R7.2, X2.14
unnamed: IC2.14 (B5), R8.1, U$8.6 (HSYNC)
unnamed: IC2.15 (B4), U$8.5 (DEN)
unnamed: D4.A, IC2.16 (B3), U$8.2 (TTLVID)
unnamed: D2.C, R15.1
unnamed: D3.C, R14.1
unnamed: D4.C, R13.1
unnamed: D7.A, R18.2
unnamed: D7.C, R19.2, U$10.2
unnamed: D3.A, IC2.17 (B2)
TTLSOUND: IC2.9 (A8); also elsewhere on the board
V33: U$8.4 (V33); also elsewhere on the board
VCC: IC2.1 (DIR), IC2.20 (VCC), U$8.9 (VCC); also elsewhere on the board
VIDEO: IC2.2 (A1), IC2.3 (A2), IC2.4 (A3); also elsewhere on the board
VSYNC: IC2.7 (A6); also elsewhere on the board

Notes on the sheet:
MICROPET-V2.1A-20220205
MICROPET-V2.1A
(C) A. Fachat
SHEET 4/5
V2.0B: do not use '245 level converter for PHI2 and PHI2_IO V2.1A: Value of R18 optionally as 2k4
Optionally R18 = 2k4

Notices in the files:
Board/micropet_v1.brd:
(C) 2020,2021 A. Fachat
